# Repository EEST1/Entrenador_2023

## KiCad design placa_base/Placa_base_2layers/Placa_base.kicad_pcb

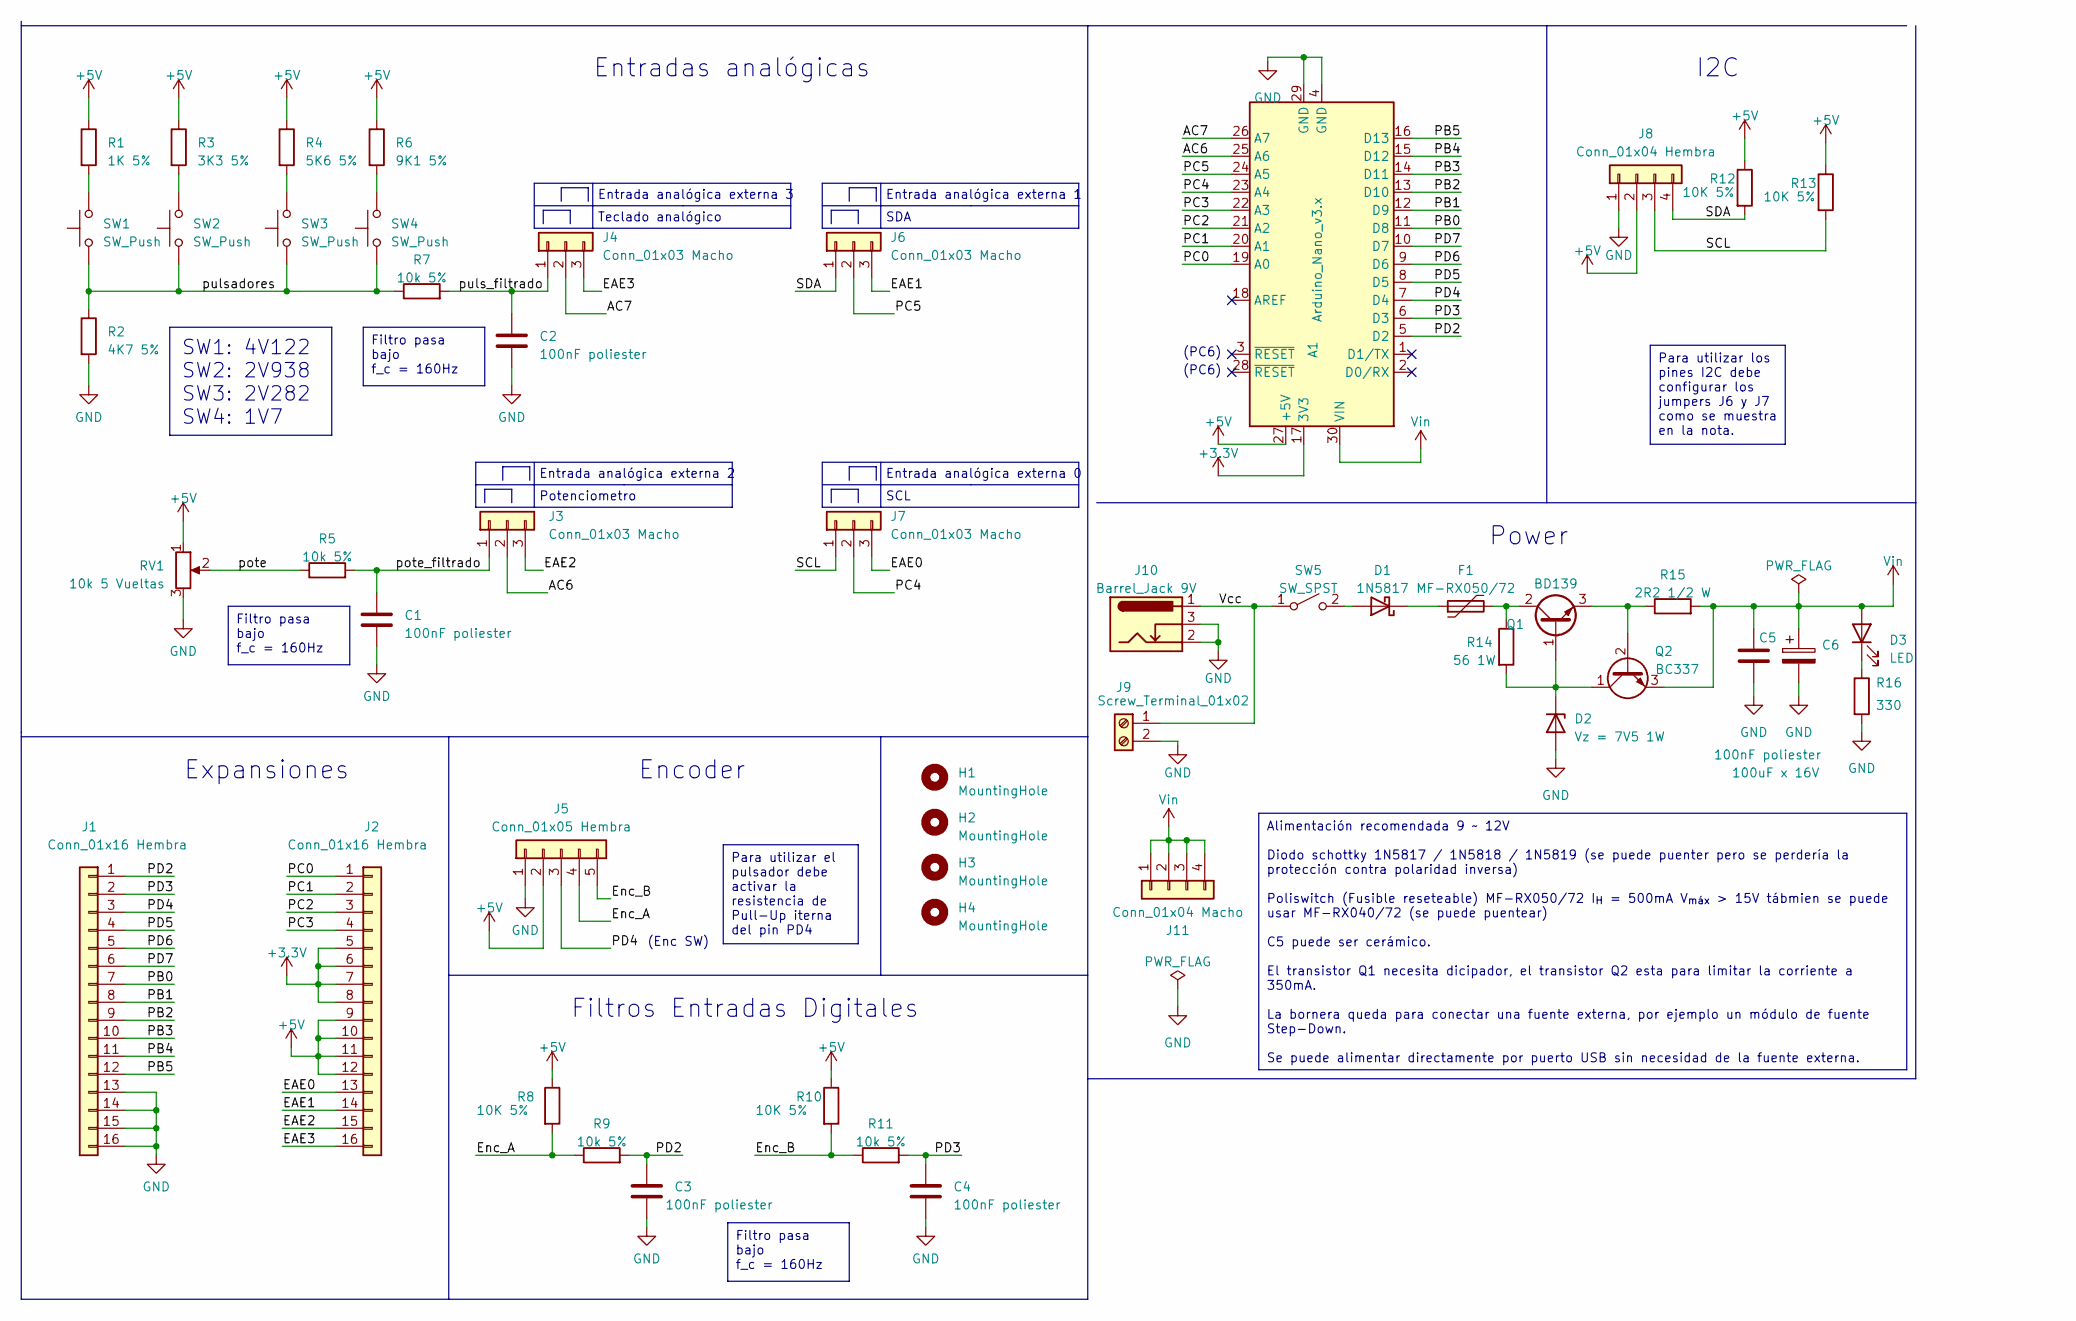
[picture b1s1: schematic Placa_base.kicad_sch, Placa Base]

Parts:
A1: Arduino_Nano_v3.x; Arduino_Nano
C1, C2, C3, C4, C5: 100nF poliester; C_Disc_D7.5mm_W5.0mm_P7.50mm
C6: 100uF x 16V; CP_Radial_D7.5mm_P2.50mm
D1: 1N5817; D_DO-41_SOD81_P10.16mm_Horizontal
D2: Vz = 7V5 1W; D_DO-41_SOD81_P12.70mm_Horizontal
D3: LED; LED_D3.0mm
F1: MF-RX050/72; Fuse_Bourns_MF-RHT050
H1, H2, H3, H4: MountingHole; MountingHole_3.2mm_M3
J1, J2: Conn_01x16 Hembra; PinSocket_1x16_P2.54mm_Vertical
J3, J4, J6, J7: Conn_01x03 Macho; PinHeader_1x03_P2.54mm_Vertical
J5: Conn_01x05 Hembra; PinSocket_1x05_P2.54mm_Vertical
J8: Conn_01x04 Hembra; PinSocket_1x04_P2.54mm_Vertical
J9: Screw_Terminal_01x02; TerminalBlock_Phoenix_PT-1,5-2-5.0-H_1x02_P5.00mm_Horizontal
J10: Barrel_Jack 9V; BarrelJack_Horizontal
J11: Conn_01x04 Macho; PinHeader_1x04_P2.54mm_Vertical
Q1: BD139; TO-126-3_Vertical
Q2: BC337; TO-92L_Wide
R1: 1K 5%; R_Axial_DIN0207_L6.3mm_D2.5mm_P10.16mm_Horizontal
R2: 4K7 5%; R_Axial_DIN0207_L6.3mm_D2.5mm_P10.16mm_Horizontal
R3: 3K3 5%; R_Axial_DIN0207_L6.3mm_D2.5mm_P10.16mm_Horizontal
R4: 5K6 5%; R_Axial_DIN0207_L6.3mm_D2.5mm_P10.16mm_Horizontal
R5, R7, R9, R11: 10k 5%; R_Axial_DIN0207_L6.3mm_D2.5mm_P10.16mm_Horizontal
R6: 9K1 5%; R_Axial_DIN0207_L6.3mm_D2.5mm_P10.16mm_Horizontal
R8, R10, R12, R13: 10K 5%; R_Axial_DIN0207_L6.3mm_D2.5mm_P10.16mm_Horizontal
R14: 56 1W; R_Axial_DIN0614_L14.3mm_D5.7mm_P25.40mm_Horizontal
R15: 2R2 1/2 W; R_Axial_DIN0309_L9.0mm_D3.2mm_P15.24mm_Horizontal
R16: 330; R_Axial_DIN0207_L6.3mm_D2.5mm_P10.16mm_Horizontal
RV1: 10k 5 Vueltas; Potentiometer_Bourns_3266Y_Vertical
SW1, SW2, SW3, SW4: SW_Push; SW_PUSH_6mm_H8mm
SW5: SW_SPST; SW_DIP_SPSTx01_Slide_9.78x4.72mm_W7.62mm_P2.54mm

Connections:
+3.3V: A1.17 (3V3), J2.5, J2.6, J2.7, J2.8
+5V: A1.27 (+5V), J2.9, J2.10, J2.11, J2.12, J5.2, J8.2, R1.1, R3.1, R4.1, R6.1, R8.1, R10.1, R12.1, R13.1, RV1.1
/AC6: A1.25 (A6), J3.2
/AC7: A1.26 (A7), J4.2
/EAE0: J2.13, J7.3
/EAE1: J2.14, J6.3
/EAE2: J2.15, J3.3
/EAE3: J2.16, J4.3
/Enc_A: J5.4, R8.2, R9.1
/Enc_B: J5.5, R10.2, R11.1
/PB0: A1.11 (D8), J1.7
/PB1: A1.12 (D9), J1.8
/PB2: A1.13 (D10), J1.9
/PB3: A1.14 (D11), J1.10
/PB4: A1.15 (D12), J1.11
/PB5: A1.16 (D13), J1.12
/PC0: A1.19 (A0), J2.1
/PC1: A1.20 (A1), J2.2
/PC2: A1.21 (A2), J2.3
/PC3: A1.22 (A3), J2.4
/PC4: A1.23 (A4), J7.2
/PC5: A1.24 (A5), J6.2
/PD2: A1.5 (D2), C3.1, J1.1, R9.2
/PD3: A1.6 (D3), C4.1, J1.2, R11.2
/PD4: A1.7 (D4), J1.3, J5.3
/PD5: A1.8 (D5), J1.4
/PD6: A1.9 (D6), J1.5
/PD7: A1.10 (D7), J1.6
/SCL: J7.1, J8.3, R13.2
/SDA: J6.1, J8.4, R12.2
/Vcc: J9.1, J10.1, SW5.1 (A)
/pote: R5.1, RV1.2
/pote_filtrado: C1.1, J3.1, R5.2
/puls_filtrado: C2.1, J4.1, R7.2
/pulsadores: R2.1, R7.1, SW1.1, SW2.1, SW3.1, SW4.1
GND: A1.4 (GND), A1.29 (GND), C1.2, C2.2, C3.2, C4.2, C5.2, C6.2, D2.2 (A), J1.13, J1.14, J1.15, J1.16, J5.1, J8.1, J9.2, J10.2, J10.3, R2.2, R16.2, RV1.3
unnamed: D1.2 (A), SW5.2 (B)
unnamed: D1.1 (K), F1.1
unnamed: D2.1 (K), Q1.1 (B), Q2.1 (C), R14.2
unnamed: D3.1 (K), R16.1
unnamed: F1.2, Q1.2 (C), R14.1
unnamed: Q1.3 (E), Q2.2 (B), R15.1
unnamed: R1.2, SW1.2
unnamed: R3.2, SW2.2
unnamed: R4.2, SW3.2
unnamed: R6.2, SW4.2
Vin: A1.30 (VIN), C5.1, C6.1, D3.2 (A), J11.1, J11.2, J11.3, J11.4, Q2.3 (E), R15.2

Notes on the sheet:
Filtro pasa bajo f_c = 160Hz
SW1: 4V122 SW2: 2V938 SW3: 2V282 SW4: 1V7
Alimentación recomendada 9 ~ 12V Diodo schottky 1N5817 / 1N5818 / 1N5819 (se puede puenter pero se perdería la protección contra polaridad inversa) Poliswitch (Fusible reseteable) MF-RX050/72 I_{H} = 500mA V_{máx} > 15V tábmien se puede usar MF-RX040/72 (se puede puentear) C5 puede ser cerámico. El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
Para utilizar el pulsador debe activar la resistencia de Pull-Up iterna del pin PD4
Para utilizar los pines I2C debe configurar los jumpers J6 y J7 como se muestra en la nota.
Entrada analógica externa 0
Entrada analógica externa 1
SCL
(PC6)
Encoder
Power
Entrada analógica externa 2
SDA
I2C
Filtros Entradas Digitales
Entrada analógica externa 3
Expansiones
Teclado analógico
(Enc SW)
Entradas analógicas
Potenciometro

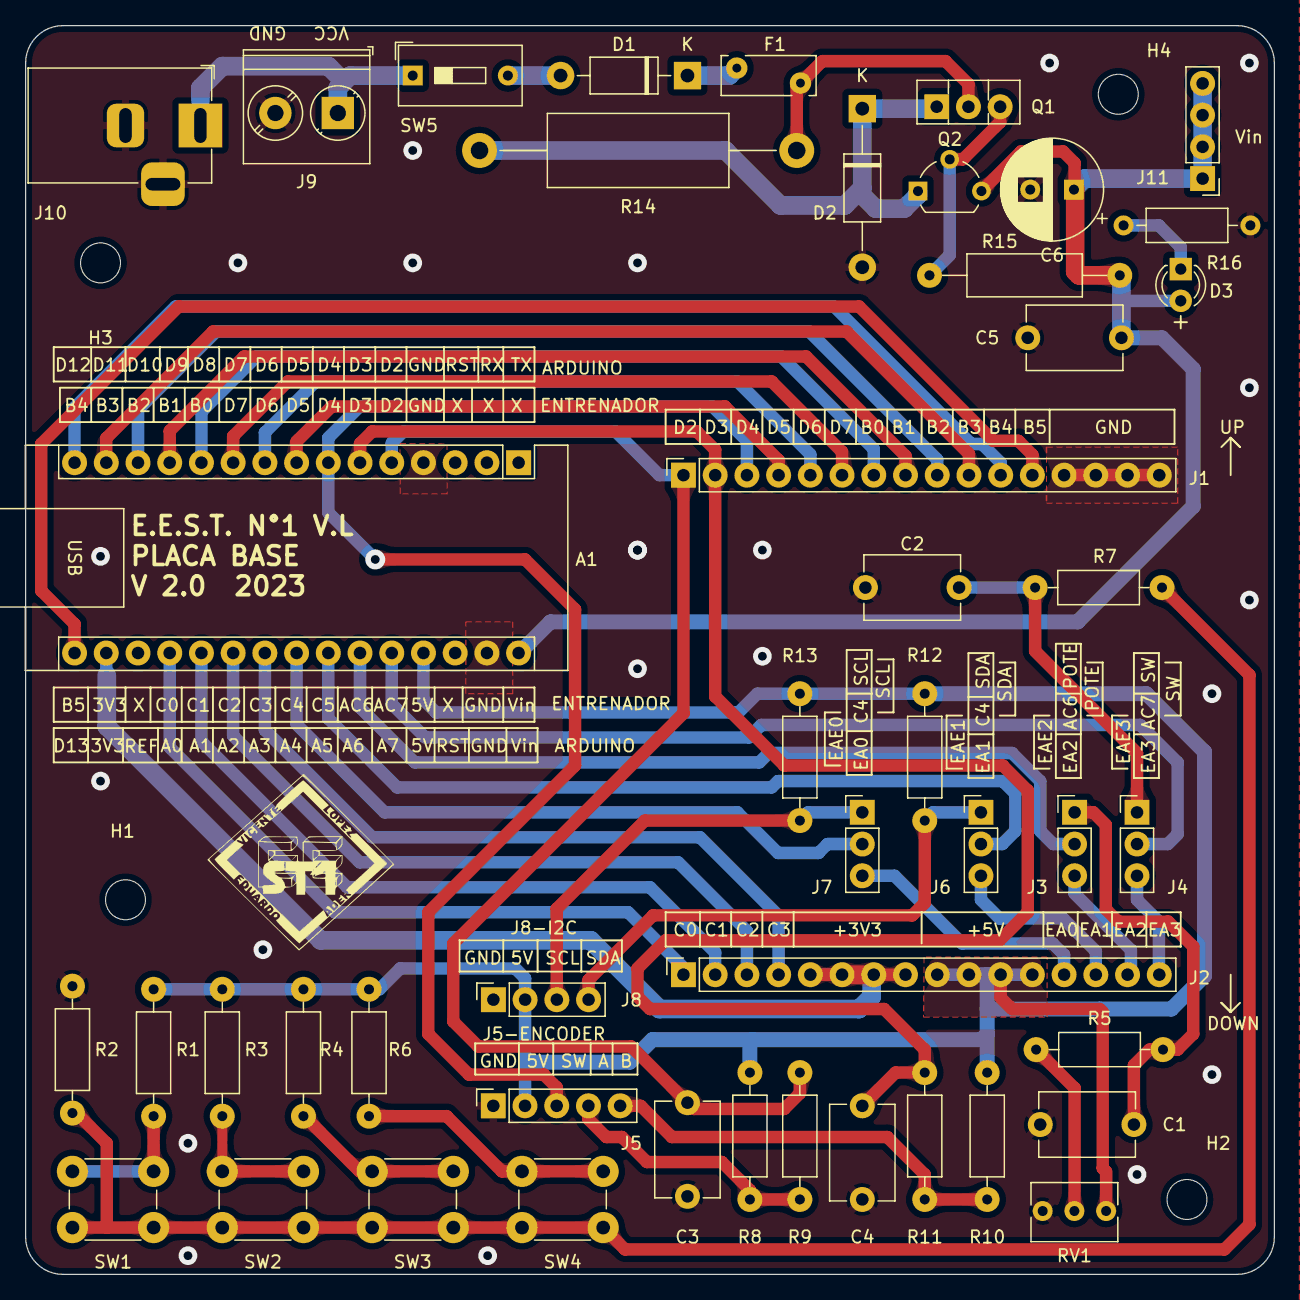
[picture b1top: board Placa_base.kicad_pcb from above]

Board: 2 copper layers, 100.0 x 100.0 mm, 50 parts (0 on the bottom side), 47 nets.

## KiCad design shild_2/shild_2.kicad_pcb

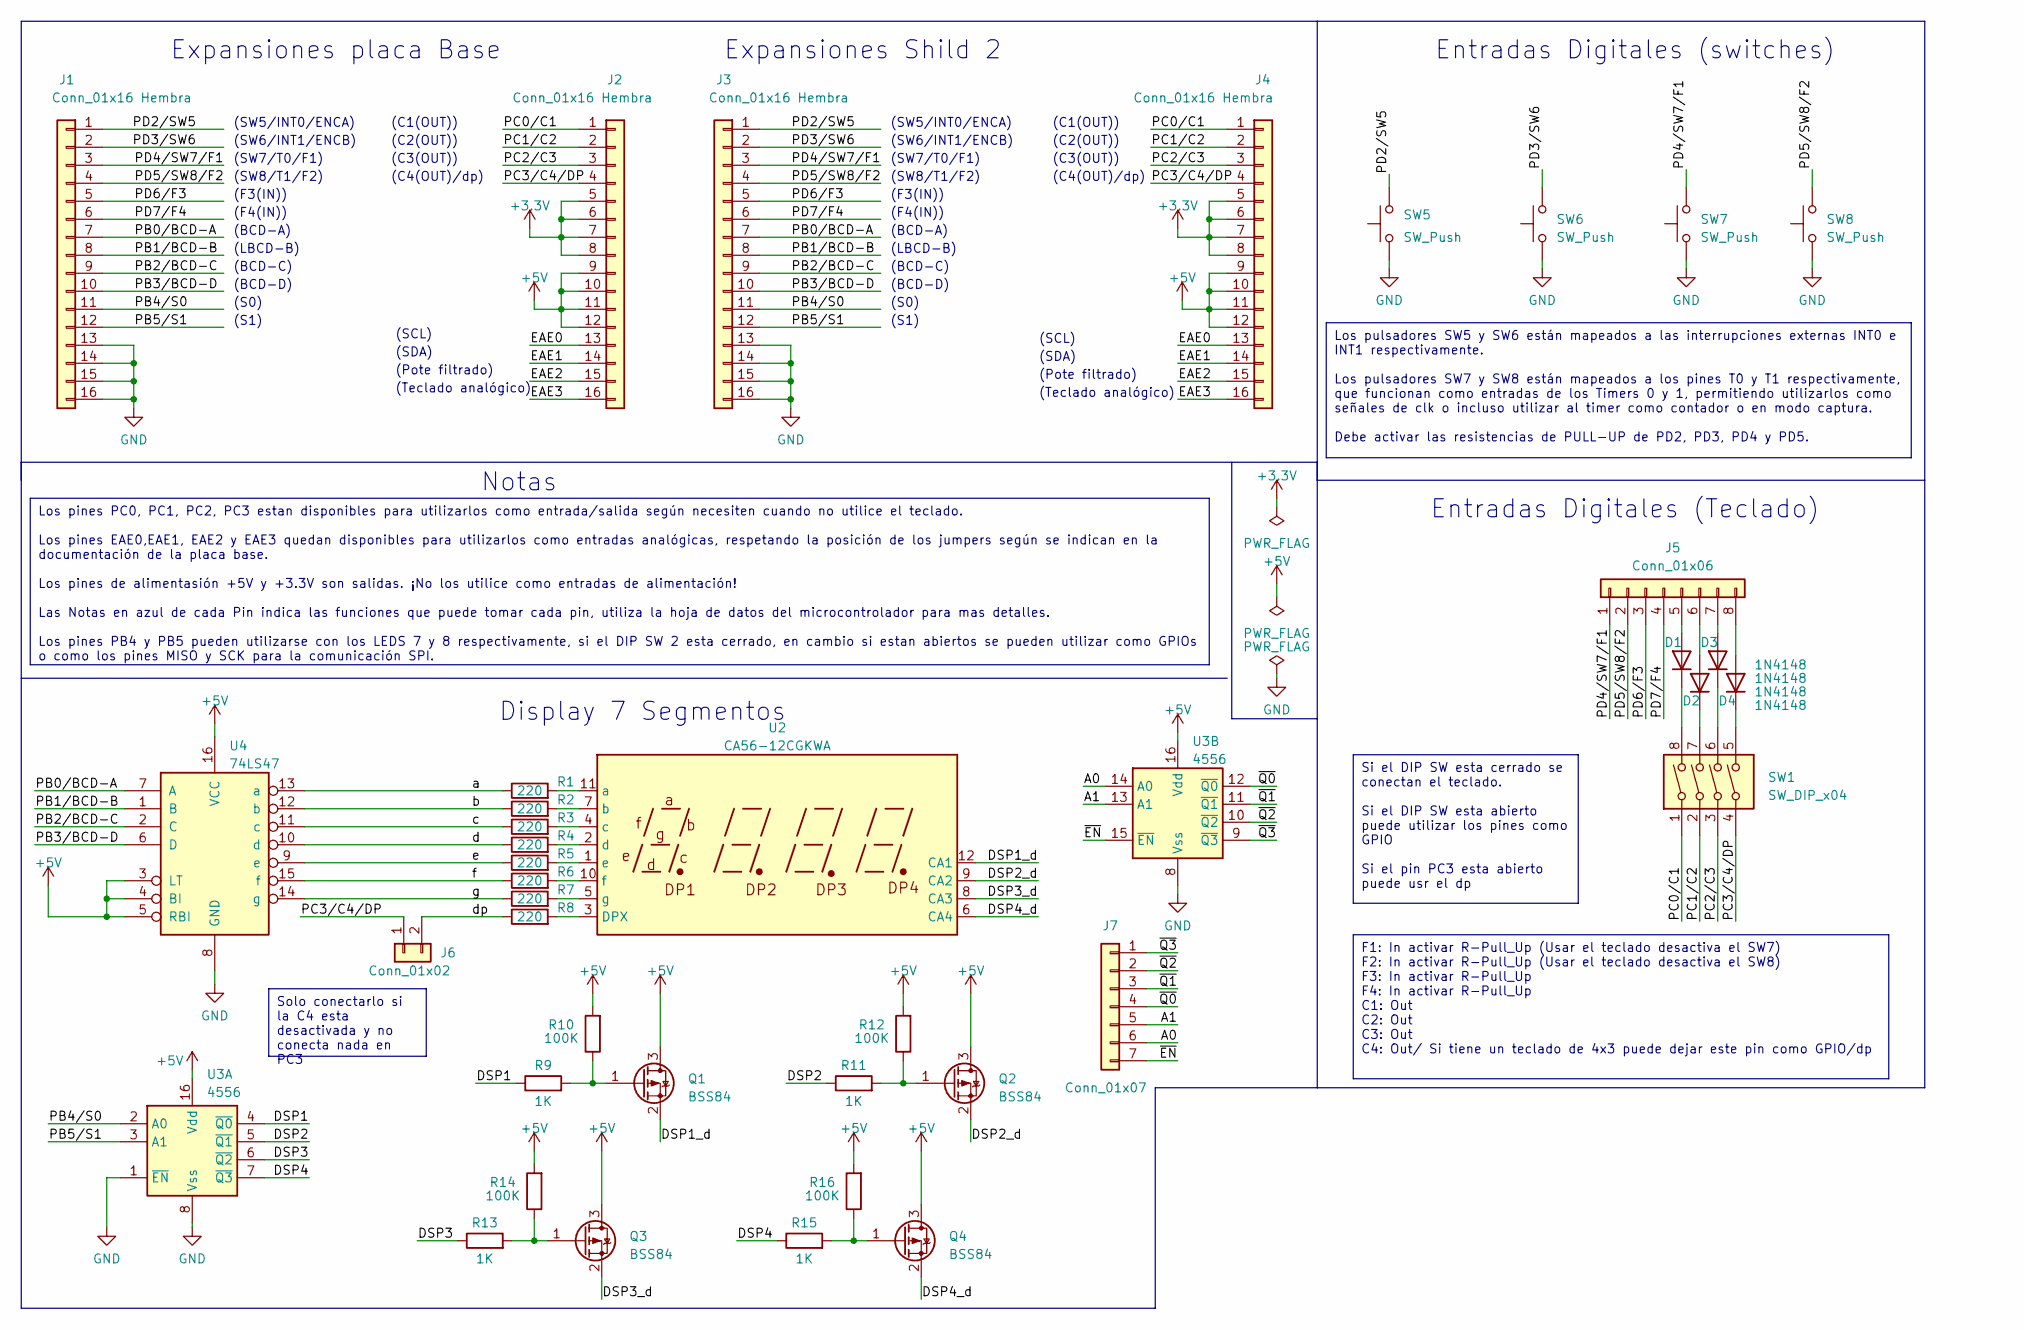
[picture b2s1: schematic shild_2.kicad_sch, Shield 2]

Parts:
D1, D2, D3, D4: 1N4148; D_DO-35_SOD27_P12.70mm_Horizontal
J1, J2: Conn_01x16 Hembra; PinHeader_1x16_P2.54mm_Vertical
J3, J4: Conn_01x16 Hembra; PinSocket_1x16_P2.54mm_Vertical
J5: Conn_01x06; PinHeader_1x08_P2.54mm_Vertical
J6: Conn_01x02; PinHeader_1x02_P2.54mm_Vertical
J7: Conn_01x07; PinHeader_1x07_P2.54mm_Vertical
Q1, Q2, Q3, Q4: BSS84; SOT-23
R1, R2, R3, R4, R5, R6, R7, R8: 220; R_Axial_DIN0309_L9.0mm_D3.2mm_P12.70mm_Horizontal
R9, R11, R13, R15: 1K; R_1206_3216Metric_Pad1.30x1.75mm_HandSolder
R10, R12, R14, R16: 100K; R_1206_3216Metric_Pad1.30x1.75mm_HandSolder
SW1: SW_DIP_x04; SW_DIP_SPSTx04_Slide_9.78x12.34mm_W7.62mm_P2.54mm
SW5, SW6, SW7, SW8: SW_Push; SW_PUSH_6mm_H8mm
U2: CA56-12CGKWA
U3: 4556; DIP-16_W7.62mm_LongPads
U4: 74LS47; DIP-16_W7.62mm_LongPads

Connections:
+3.3V: J2.5, J2.6, J2.7, J2.8, J4.5, J4.6, J4.7, J4.8
+5V: J2.9, J2.10, J2.11, J2.12, J4.9, J4.10, J4.11, J4.12, Q1.3 (D), Q2.3 (D), Q3.3 (D), Q4.3 (D), R10.2, R12.2, R14.2, R16.2, U3.16 (Vdd), U4.3 (LT), U4.4 (BI), U4.5 (RBI), U4.16 (VCC)
/A0: J7.6, U3.14 (A0)
/A1: J7.5, U3.13 (A1)
/DSP1: R9.1, U3.4 (~Q0)
/DSP1_d: Q1.2 (S), U2.12 (CA1)
/DSP2: R11.1, U3.5 (~Q1)
/DSP2_d: Q2.2 (S), U2.9 (CA2)
/DSP3: R13.1, U3.6 (~Q2)
/DSP3_d: Q3.2 (S), U2.8 (CA3)
/DSP4: R15.1, U3.7 (~Q3)
/DSP4_d: Q4.2 (S), U2.6 (CA4)
/EAE0: J2.13, J4.13
/EAE1: J2.14, J4.14
/EAE2: J2.15, J4.15
/EAE3: J2.16, J4.16
/PB0/BCD-A: J1.7, J3.7, U4.7 (A)
/PB1/BCD-B: J1.8, J3.8, U4.1 (B)
/PB2/BCD-C: J1.9, J3.9, U4.2 (C)
/PB3/BCD-D: J1.10, J3.10, U4.6 (D)
/PB4/S0: J1.11, J3.11, U3.2 (A0)
/PB5/S1: J1.12, J3.12, U3.3 (A1)
/PC0/C1: J2.1, J4.1, SW1.1
/PC1/C2: J2.2, J4.2, SW1.2
/PC2/C3: J2.3, J4.3, SW1.3
/PC3/C4/DP: J2.4, J4.4, J6.1, SW1.4
/PD2/SW5: J1.1, J3.1, SW5.2
/PD3/SW6: J1.2, J3.2, SW6.2
/PD4/SW7/F1: J1.3, J3.3, J5.1, SW7.2
/PD5/SW8/F2: J1.4, J3.4, J5.2, SW8.2
/PD6/F3: J1.5, J3.5, J5.3
/PD7/F4: J1.6, J3.6, J5.4
/a: R1.1, U4.13 (a)
/b: R2.1, U4.12 (b)
/c: R3.1, U4.11 (c)
/d: R4.1, U4.10 (d)
/dp: J6.2, R8.1
/e: R5.1, U4.9 (e)
/f: R6.1, U4.15 (f)
/g: R7.1, U4.14 (g)
/~EN: J7.7, U3.15 (~EN)
/~Q0: J7.4, U3.12 (~Q0)
/~Q1: J7.3, U3.11 (~Q1)
/~Q2: J7.2, U3.10 (~Q2)
/~Q3: J7.1, U3.9 (~Q3)
GND: J1.13, J1.14, J1.15, J1.16, J3.13, J3.14, J3.15, J3.16, SW5.1, SW6.1, SW7.1, SW8.1, U3.1 (~EN), U3.8 (Vss), U4.8 (GND)
unnamed: D1.2 (A), J5.5
unnamed: D1.1 (K), SW1.8
unnamed: D2.2 (A), J5.6
unnamed: D2.1 (K), SW1.7
unnamed: D3.2 (A), J5.7
unnamed: D3.1 (K), SW1.6
unnamed: D4.2 (A), J5.8
unnamed: D4.1 (K), SW1.5
unnamed: Q1.1 (G), R9.2, R10.1
unnamed: Q2.1 (G), R11.2, R12.1
unnamed: Q3.1 (G), R13.2, R14.1
unnamed: Q4.1 (G), R15.2, R16.1
unnamed: R8.2, U2.3 (DPX)
unnamed: R1.2, U2.11 (a)
unnamed: R2.2, U2.7 (b)
unnamed: R3.2, U2.4 (c)
unnamed: R4.2, U2.2 (d)
unnamed: R5.2, U2.1 (e)
unnamed: R6.2, U2.10 (f)
unnamed: R7.2, U2.5 (g)

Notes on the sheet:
Si el DIP SW esta cerrado se conectan el teclado. Si el DIP SW esta abierto puede utilizar los pines como GPIO Si el pin PC3 esta abierto puede usr el dp
Los pines PC0, PC1, PC2, PC3 estan disponibles para utilizarlos como entrada/salida según necesiten cuando no utilice el teclado. Los pines EAE0,EAE1, EAE2 y EAE3 quedan disponibles para utilizarlos como entradas analógicas, respetando la posición de los jumpers según se indican en la documentación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
Los pulsadores SW5 y SW6 están mapeados a las interrupciones externas INT0 e INT1 respectivamente. Los pulsadores SW7 y SW8 están mapeados a los pines T0 y T1 respectivamente, que funcionan como entradas de los Timers 0 y 1, permitiendo utilizarlos como señales de clk o incluso utilizar al timer co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
F1: In activar R-Pull_Up (Usar el teclado desactiva el SW7) F2: In activar R-Pull_Up (Usar el teclado desactiva el SW8) F3: In activar R-Pull_Up F4: In activar R-Pull_Up C1: Out C2: Out C3: Out C4: Out/ Si tiene un teclado de 4x3 puede dejar este pin como GPIO/dp
Solo conectarlo si la C4 esta desactivada y no conecta nada en PC3
(SW6/INT1/ENCB)
(F4(IN))
(C2(OUT))
(SW5/INT0/ENCA)
(SW7/T0/F1)
(SDA)
(Teclado analógico)
(SCL)
(S0)
(BCD-A)
(C3(OUT))
(LBCD-B)
Expansiones Shild 2
(F3(IN))
(Pote filtrado)
Entradas Digitales (Teclado)
(C4(OUT)/dp)
(SW8/T1/F2)
(C1(OUT))
Notas
Display 7 Segmentos
(S1)
Expansiones placa Base
Entradas Digitales (switches)
(BCD-C)
(BCD-D)

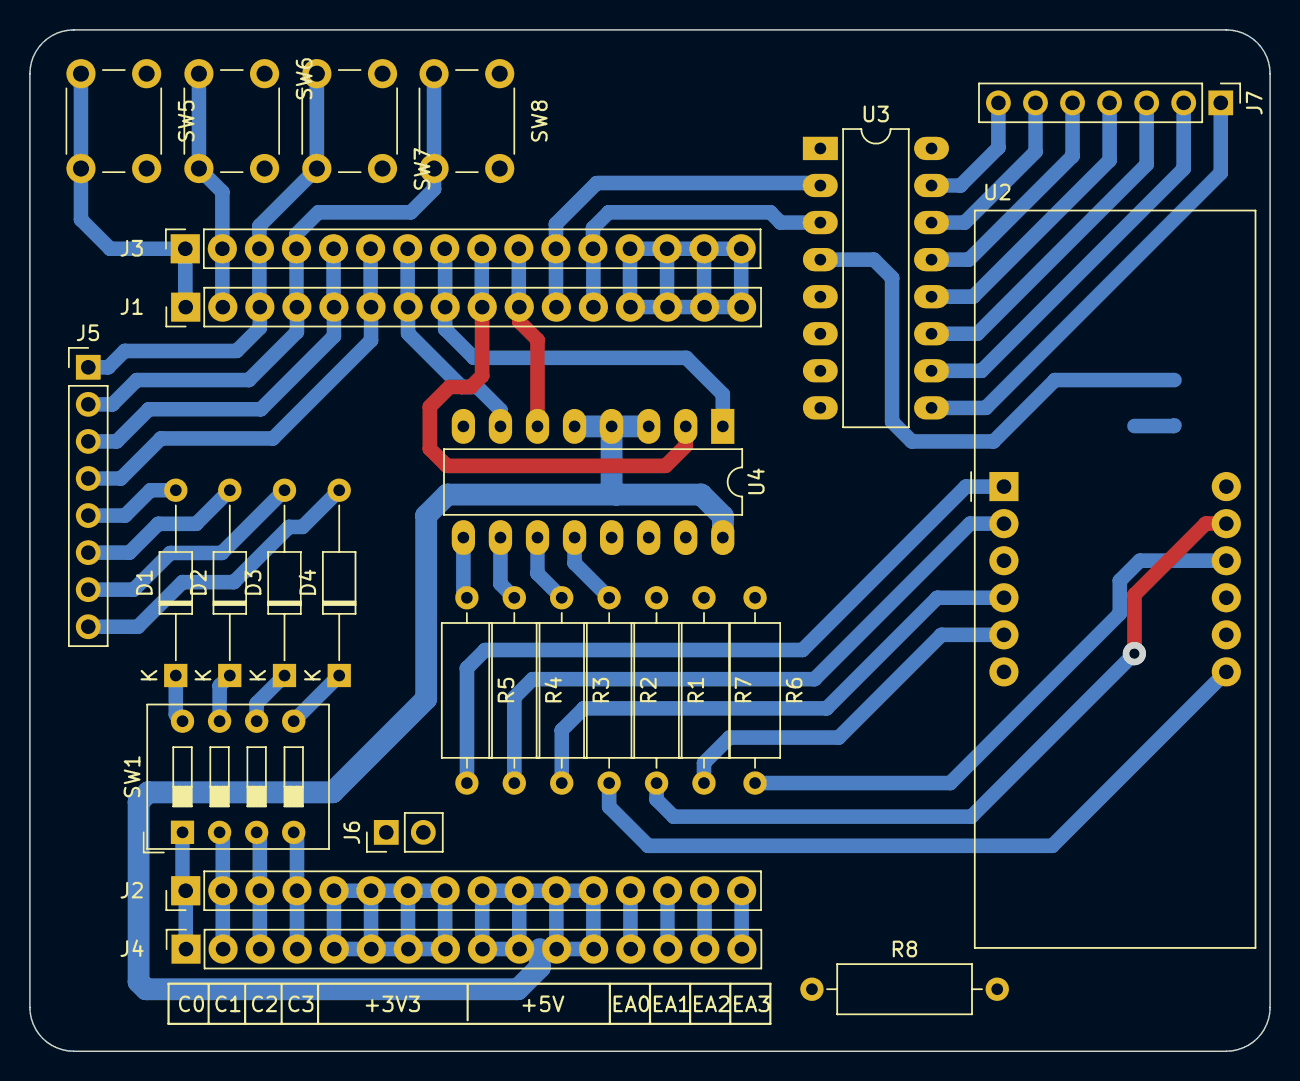
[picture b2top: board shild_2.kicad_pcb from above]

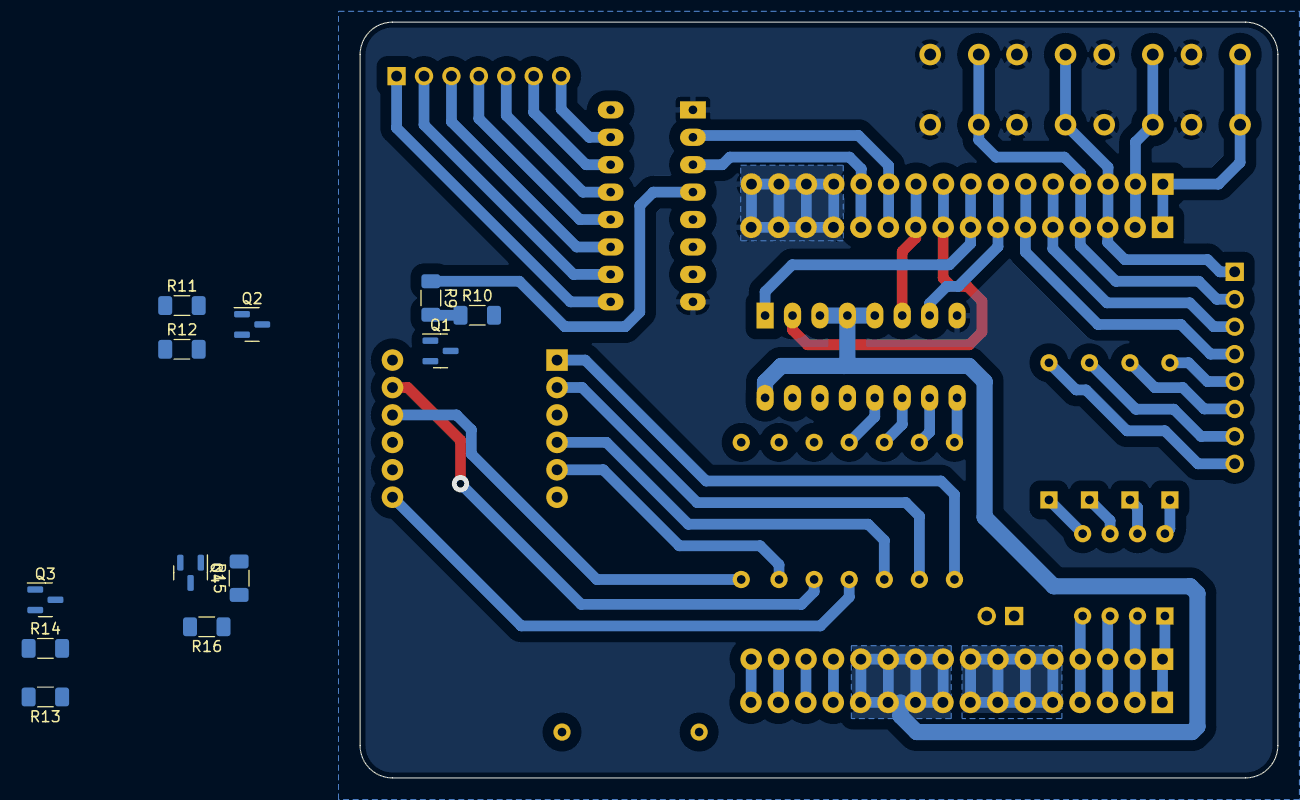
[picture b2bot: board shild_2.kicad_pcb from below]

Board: 2 copper layers, 85.0 x 70.0 mm, 39 parts (12 on the bottom side), 66 nets.

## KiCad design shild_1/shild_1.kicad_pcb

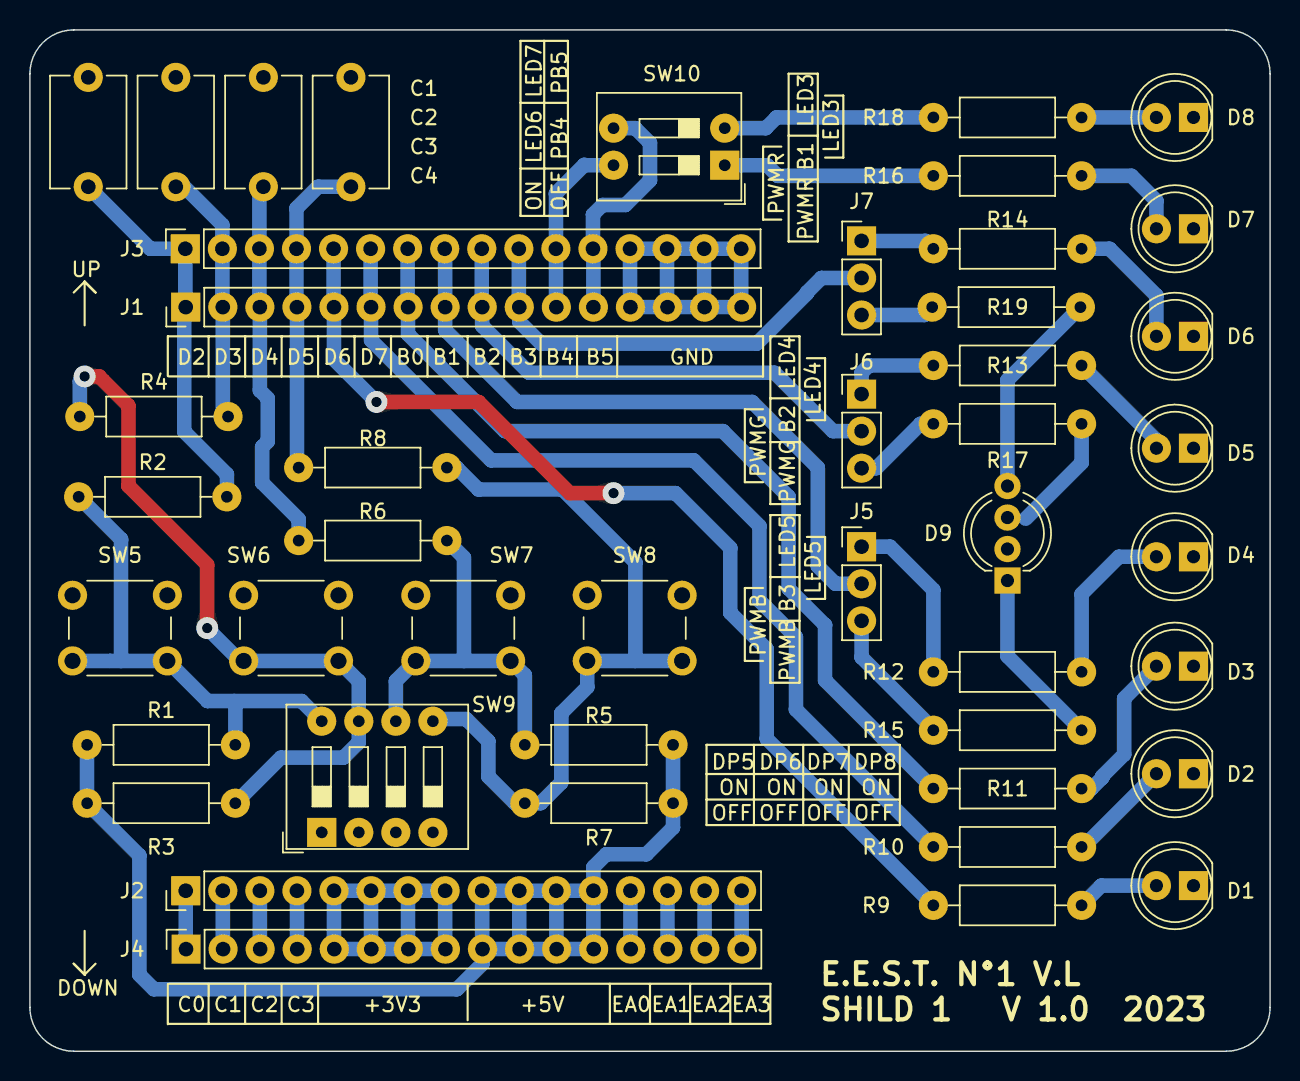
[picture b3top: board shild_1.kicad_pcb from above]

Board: 2 copper layers, 85.0 x 70.0 mm, 45 parts (0 on the bottom side), 46 nets.

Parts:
C1, C2, C3, C4: 100nF poliester; C_Disc_D7.5mm_W5.0mm_P7.50mm
D1: LED0; LED_D5.0mm
D2: LED1; LED_D5.0mm
D3: LED2; LED_D5.0mm
D4: LED3; LED_D5.0mm
D5: LED4; LED_D5.0mm
D6: LED5; LED_D5.0mm
D7: LED6; LED_D5.0mm
D8: LED7; LED_D5.0mm
D9: LED_RKGB; LED_D5.0mm-4_RGB_Wide_Pins
J1, J2: Conn_01x16 Hembra; PinHeader_1x16_P2.54mm_Vertical
J3, J4: Conn_01x16 Hembra; PinSocket_1x16_P2.54mm_Vertical
J5, J6, J7: Conn_01x03 Macho; PinHeader_1x03_P2.54mm_Vertical
R1, R3, R5, R7: 10K 5%; R_Axial_DIN0207_L6.3mm_D2.5mm_P10.16mm_Horizontal
R2, R4, R6, R8: 10k 5%; R_Axial_DIN0207_L6.3mm_D2.5mm_P10.16mm_Horizontal
R9, R10, R11, R12, R13, R14, R15, R16, R17, R18, R19: 220; R_Axial_DIN0207_L6.3mm_D2.5mm_P10.16mm_Horizontal
SW5, SW6, SW7, SW8: SW_Push; SW_PUSH_6mm_H8mm
SW9: SW_DIP_x04; SW_DIP_SPSTx04_Slide_9.78x12.34mm_W7.62mm_P2.54mm
SW10: SW_DIP_x02; SW_DIP_SPSTx02_Slide_9.78x7.26mm_W7.62mm_P2.54mm

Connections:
+3.3V: J2.5, J2.6, J2.7, J2.8, J4.5, J4.6, J4.7, J4.8
+5V: J2.9, J2.10, J2.11, J2.12, J4.9, J4.10, J4.11, J4.12, R1.1, R3.1, R5.1, R7.1
/DP5: R1.2, R2.1, SW5.2, SW9.8
/DP6: R3.2, R4.1, SW6.2, SW9.7
/DP7: R5.2, R6.1, SW7.2, SW9.6
/DP8: R7.2, R8.1, SW8.2, SW9.5
/EAE0: J2.13, J4.13
/EAE1: J2.14, J4.14
/EAE2: J2.15, J4.15
/EAE3: J2.16, J4.16
/LED3: J5.1, R12.1
/LED4: J6.1, R13.1
/LED5: J7.1, R14.1
/LED6: R16.1, SW10.1
/LED7: R18.1, SW10.2
/PB0/LED2: J1.7, J3.7, R11.1
/PB1: J1.8, J3.8, J5.2
/PB2: J1.9, J3.9, J6.2
/PB3: J1.10, J3.10, J7.2
/PB4: J1.11, J3.11, SW10.4
/PB5: J1.12, J3.12, SW10.3
/PC0: J2.1, J4.1
/PC1: J2.2, J4.2
/PC2: J2.3, J4.3
/PC3: J2.4, J4.4
/PD2/SW5/DP5: C1.1, J1.1, J3.1, R2.2
/PD3/SW6/DP6: C2.1, J1.2, J3.2, R4.2
/PD4/SW7/DP7: C3.1, J1.3, J3.3, R6.2
/PD5/SW8/DP8: C4.1, J1.4, J3.4, R8.2
/PD6/LED0: J1.5, J3.5, R9.1
/PD7/LED1: J1.6, J3.6, R10.1
/PWM-B: J7.3, R19.1
/PWM-G: J6.3, R17.1
/PWM-R: J5.3, R15.1
GND: C1.2, C2.2, C3.2, C4.2, D1.1 (K), D2.1 (K), D3.1 (K), D4.1 (K), D5.1 (K), D6.1 (K), D7.1 (K), D8.1 (K), D9.2 (K), J1.13, J1.14, J1.15, J1.16, J3.13, J3.14, J3.15, J3.16, SW5.1, SW6.1, SW7.1, SW8.1, SW9.1, SW9.2, SW9.3, SW9.4
unnamed: D1.2 (A), R9.2
unnamed: D2.2 (A), R10.2
unnamed: D3.2 (A), R11.2
unnamed: D4.2 (A), R12.2
unnamed: D5.2 (A), R13.2
unnamed: D6.2 (A), R14.2
unnamed: D7.2 (A), R16.2
unnamed: D8.2 (A), R18.2
unnamed: D9.4 (BA), R19.2
unnamed: D9.3 (GA), R17.2
unnamed: D9.1 (RA), R15.2

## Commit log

2023-05-10 Changes to be committed: new file: desktop.ini new file: placa_base/Draft1.asc new file: placa_base/Placa_base_2layers/#auto_saved_files# new file: placa_base/Placa_base_2layers/Documentacion/Captura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
2023-05-10 Changes to be committed: new file: placa_base/Placa_base_2layers/fabrication/gerbers/10Mayo2023/Placa_base-B_Cu.gbr new file: placa_base/Placa_base_2layers/fabrication/gerbers/10Mayo2023/Placa_base-E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
2023-05-21 Please enter the commit message for your changes. Lines starting with '#' will be ignored, and an empty message aborts the commit.
    On branch master
    Your branch is up to date with 'Entrenador2023/master'.
    Changes to be committed:
    modified: desktop.ini
    deleted: placa_base/Placa_base_2layers/#auto_saved_files#
    modified: placa_base/Placa_base_2layers/Documentacion/datasheets/desktop.ini
